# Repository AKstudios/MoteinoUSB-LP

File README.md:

# MoteinoUSB-LP
Moteino USB (R5) with a unidirectional voltage level shifter (TI [SN74LVC1T45](http://www.ti.com/lit/ds/symlink/sn74lvc1t45.pdf)) to isolate current sources. This prevents parasitic current draw through FTDI's RX pin when USB is unplugged and lowers overall sleep current draw to almost the same as a base Moteino without FTDI. Measured current draw with voltage level shifter: ~6.6uA.

Alternative design using an N-channel MOSFET for voltage level shifting also included. This is cheaper than using the level shifter and lowers the current draw to ~6.4uA.

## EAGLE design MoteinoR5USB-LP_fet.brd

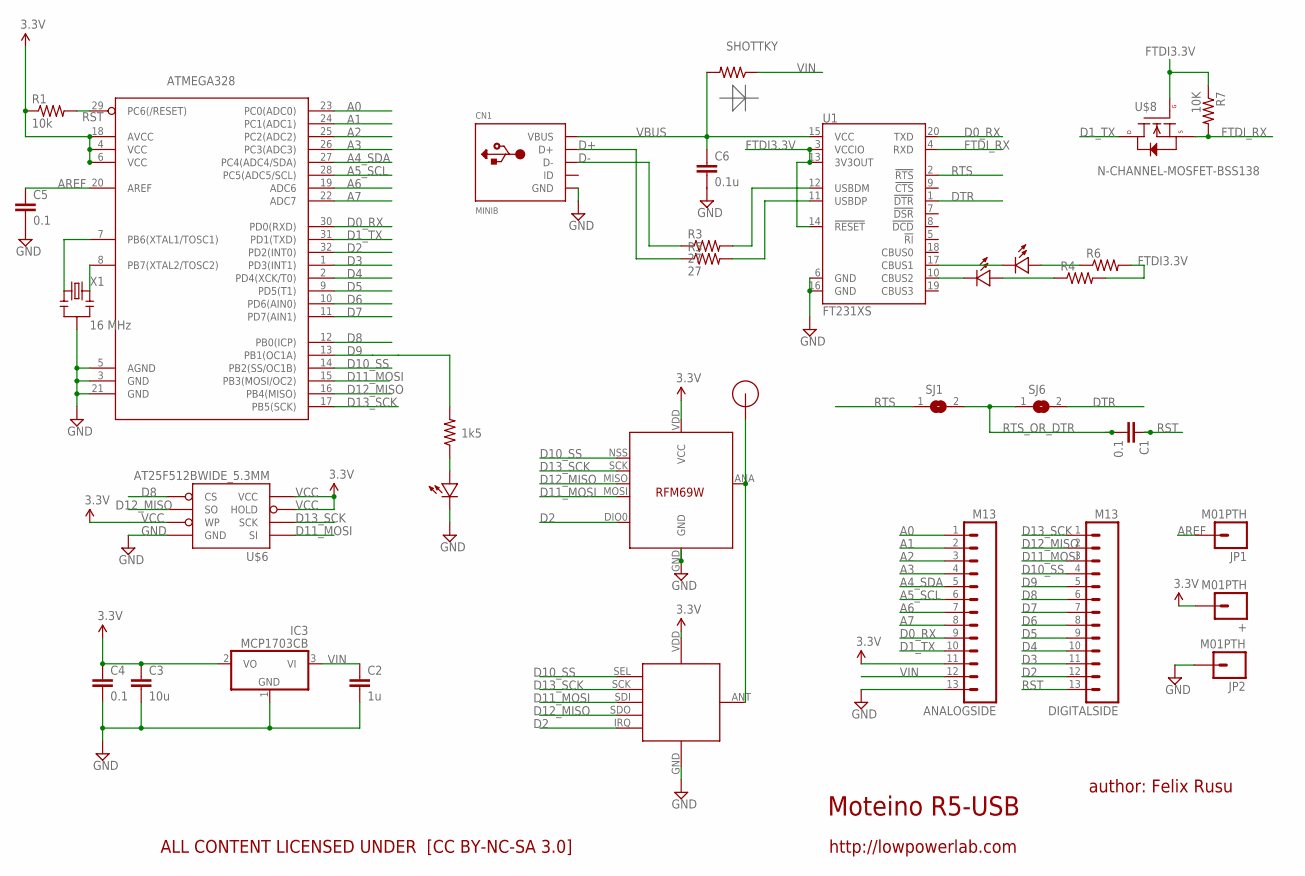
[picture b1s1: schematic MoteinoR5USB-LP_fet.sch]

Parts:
+: M01PTH; 1X01
ANALOGSIDE: M13; 1X13
ATMEGA328: ATMega-328; TQFP32-08
C1, C4, C5: 0.1; 0603-CAP
C2: 1u; 0603-CAP
C3: 10u; 0805-CAP
C6: 0.1u; 0603-CAP
CN1: MINIB; USB-MINIB
D: SHOTTKY; 0603-RES
DIGITALSIDE: M13; 1X13
IC3: MCP1703CB; SOT23
JP1, JP2: M01PTH; 1X01
R1: 10k; 0603-RES
R2: 1k5; 0603-RES
R3, R5: 27; 0603-RES
R4, R6: RESISTOR0603-RES; 0603-RES
R7: 10K; R0805
RFM12B: RFM12B_MINPADS; RFM12B-MINPADS
SJ1, SJ6: JUMPER; SJW
U1: FT231XS; SSOP20_L
U$1: RFM12B_ANTENNA; RFM12B-ANTENNA
U$2, U$4, U$7: LED0603; 0603-LED
U$5: RFM69; RFM69W-MINPADS
U$6: AT25F512BWIDE_5.3MM; SO08WIDE
U$8: N-CHANNEL-MOSFET-BSS138; SOT23-3
X1: 16 MHz; RESONATOR-SMD

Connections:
A0: ANALOGSIDE.1, ATMEGA328.23 (PC0(ADC0))
A1: ANALOGSIDE.2, ATMEGA328.24 (PC1(ADC1))
A2: ANALOGSIDE.3, ATMEGA328.25 (PC2(ADC2))
A3: ANALOGSIDE.4, ATMEGA328.26 (PC3(ADC3))
A4_SDA: ANALOGSIDE.5, ATMEGA328.27 (PC4(ADC4/SDA))
A5_SCL: ANALOGSIDE.6, ATMEGA328.28 (PC5(ADC5/SCL))
A6: ANALOGSIDE.7, ATMEGA328.19 (ADC6)
A7: ANALOGSIDE.8, ATMEGA328.22 (ADC7)
AREF: ATMEGA328.20 (AREF), C5.1, JP1.1
D0_RX: ANALOGSIDE.9, ATMEGA328.30 (PD0(RXD)), U1.20 (TXD)
D1_TX: ANALOGSIDE.10, ATMEGA328.31 (PD1(TXD)), U$8.3 (D)
D2: ATMEGA328.32 (PD2(INT0)), DIGITALSIDE.12, RFM12B.IRQ, U$5.DIO0
D3: ATMEGA328.1 (PD3(INT1)), DIGITALSIDE.11
D4: ATMEGA328.2 (PD4(XCK/T0)), DIGITALSIDE.10
D5: ATMEGA328.9 (PD5(T1)), DIGITALSIDE.9
D6: ATMEGA328.10 (PD6(AIN0)), DIGITALSIDE.8
D7: ATMEGA328.11 (PD7(AIN1)), DIGITALSIDE.7
D8: ATMEGA328.12 (PB0(ICP)), DIGITALSIDE.6, U$6.1 (CS)
D9: ATMEGA328.13 (PB1(OC1A)), DIGITALSIDE.5, R2.2
D10_SS: ATMEGA328.14 (PB2(SS/OC1B)), DIGITALSIDE.4, RFM12B.SEL, U$5.NSS (SEL)
D11_MOSI: ATMEGA328.15 (PB3(MOSI/OC2)), DIGITALSIDE.3, RFM12B.SDI (SDI/MOSI), U$5.MOSI, U$6.5 (SI)
D12_MISO: ATMEGA328.16 (PB4(MISO)), DIGITALSIDE.2, RFM12B.SDO (SDO/MISO), U$5.MISO, U$6.2 (SO)
D13_SCK: ATMEGA328.17 (PB5(SCK)), DIGITALSIDE.1, RFM12B.SCK, U$5.SCK, U$6.6 (SCK)
D+: CN1.D+, R5.1
D-: CN1.D-, R3.1
DTR: SJ6.2, U1.1 (!DTR)
FTDI3.3V: R4.2, R6.2, R7.1, U1.3 (VCCIO), U1.13 (3V3OUT), U1.14 (!RESET), U$8.1 (G)
FTDI_RX: R7.2, U1.4 (RXD), U$8.2 (S)
GND: ANALOGSIDE.13, ATMEGA328.3 (GND), ATMEGA328.5 (AGND), ATMEGA328.21 (GND), C2.2, C3.2, C4.2, C5.2, C6.2, CN1.GND, IC3.1 (GND), JP2.1, RFM12B.GND, U1.6 (GND), U1.16 (GND), U$2.MINUS, U$5.GND, U$6.4 (GND), X1.2
unnamed: ATMEGA328.7 (PB6(XTAL1/TOSC1)), X1.1
unnamed: R2.1, U$2.PLUS
unnamed: RFM12B.ANT, U$1.P$1, U$5.ANA (ANT)
unnamed: R3.2, U1.12 (USBDM)
unnamed: R5.2, U1.11 (USBDP)
unnamed: U1.17 (CBUS1), U$4.MINUS
unnamed: U1.10 (CBUS2), U$7.MINUS
unnamed: R4.1, U$7.PLUS
unnamed: R6.1, U$4.PLUS
unnamed: ATMEGA328.8 (PB7(XTAL2/TOSC2)), X1.3
RST: ATMEGA328.29 (PC6(/RESET)), C1.1, DIGITALSIDE.13, R1.2
RTS: SJ1.1, U1.2 (!RTS)
RTS_OR_DTR: C1.2, SJ1.2, SJ6.1
VBUS: C6.1, CN1.VBUS, D.2, U1.15 (VCC)
VCC: +.1, ANALOGSIDE.11, ATMEGA328.4 (VCC), ATMEGA328.6 (VCC), ATMEGA328.18 (AVCC), C3.1, C4.1, IC3.2 (VO), R1.1, RFM12B.VDD, U$5.VDD (VCC), U$6.3 (WP), U$6.7 (HOLD), U$6.8 (VCC)
VIN: ANALOGSIDE.12, C2.1, D.1, IC3.3 (VI)

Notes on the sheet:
Moteino R5-USB
author: Felix Rusu
http://lowpowerlab.com
ALL CONTENT LICENSED UNDER [CC BY-NC-SA 3.0]

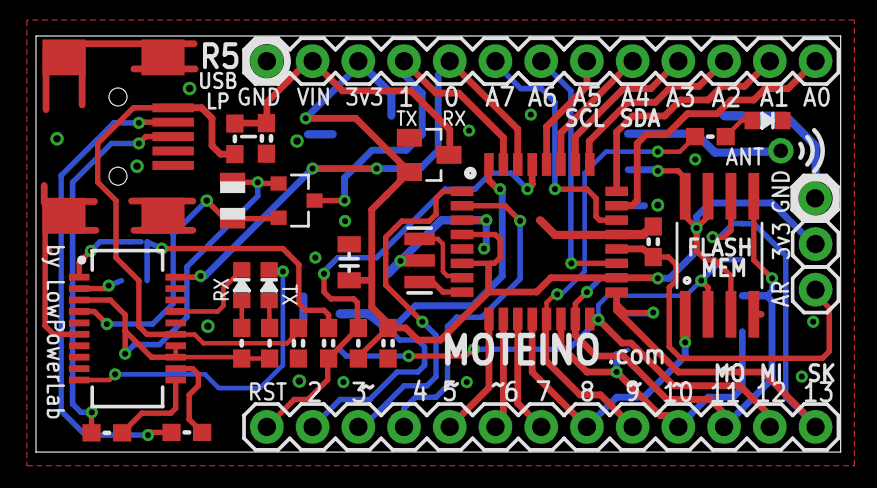
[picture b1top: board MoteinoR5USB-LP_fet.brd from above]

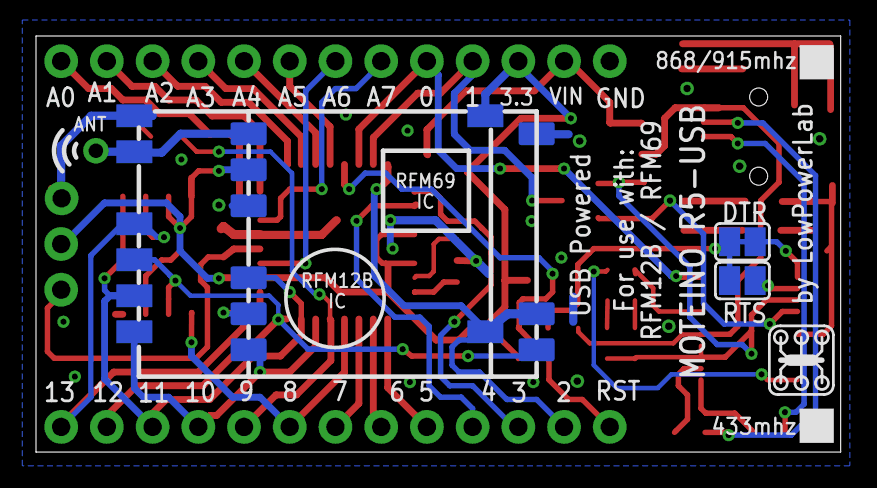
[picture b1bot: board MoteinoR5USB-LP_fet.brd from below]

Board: 2 copper layers, 44.7 x 23.1 mm, 35 parts (5 on the bottom side), 45 nets.

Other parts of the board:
U$3: LOGO_LOWPOWERLAB

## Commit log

2017-05-12 :boom::camel: Added .gitattributes & .gitignore files
2017-05-12 Uploaded EAGLE files
2018-02-06 Added a MOSFET variant
    - replaced voltage shifter with mosfet
    - some trace & silkscreen adjustments on both boards

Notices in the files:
parts and their libraries:
SparkFun-Connectors: Licensing: CC v3.0 Share-Alike You are welcome to use this library for commercial purposes.
GeekAmmo: Licensing:Creative Commons ShareAlike 4.0 International - https://creativecommons.org/licenses/by-sa/4.0
